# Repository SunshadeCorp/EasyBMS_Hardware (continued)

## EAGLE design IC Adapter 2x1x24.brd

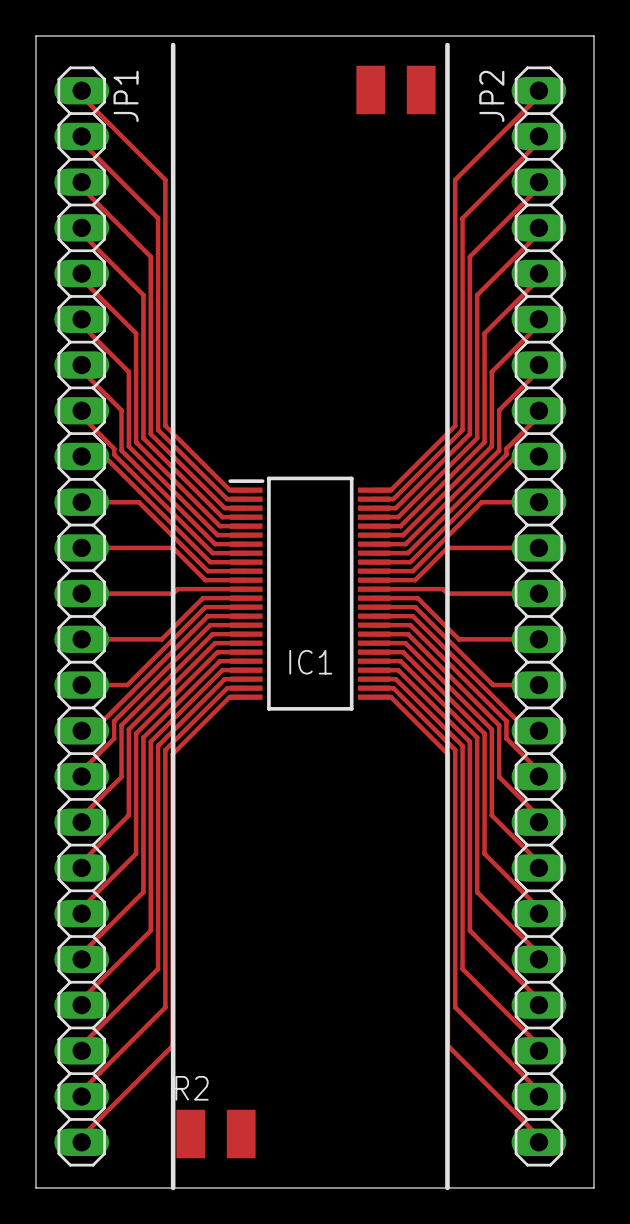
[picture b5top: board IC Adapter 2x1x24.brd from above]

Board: 2 copper layers, 31.0 x 64.0 mm, 5 parts (0 on the bottom side), 48 nets.

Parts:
IC1: LTC6804IG-1#PBF; SOP50P780X200-48N
JP1, JP2: 1X24
R1, R2: R1210

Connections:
C0: IC1.26, JP2.23
C1: IC1.24, JP1.24
C2: IC1.22, JP1.22
C3: IC1.20, JP1.20
C4: IC1.18, JP1.18
C5: IC1.16, JP1.16
C6: IC1.14, JP1.14
C7: IC1.12, JP1.12
C8: IC1.10, JP1.10
C9: IC1.8, JP1.8
C10: IC1.6, JP1.6
C11: IC1.4, JP1.4
C12: IC1.2, JP1.2
CPIO3: IC1.29, JP2.20
CSB: IC1.41, JP2.8
DRIVE: IC1.38, JP2.11
GPIO1: IC1.27, JP2.22
GPIO2: IC1.28, JP2.21
GPIO4: IC1.32, JP2.17
GPIO5: IC1.33, JP2.16
IBIAS: IC1.45, JP2.4
ICMP: IC1.46, JP2.3
IMB: IC1.47, JP2.2
IPB: IC1.48, JP2.1
ISOMD: IC1.40, JP2.9
S1: IC1.25, JP2.24
S2: IC1.23, JP1.23
S3: IC1.21, JP1.21
S4: IC1.19, JP1.19
S5: IC1.17, JP1.17
S6: IC1.15, JP1.15
S7: IC1.13, JP1.13
S8: IC1.11, JP1.11
S9: IC1.9, JP1.9
S10: IC1.7, JP1.7
S11: IC1.5, JP1.5
S12: IC1.3, JP1.3
SCK: IC1.42, JP2.7
SDI: IC1.43, JP2.6
SDO: IC1.44, JP2.5
SWTEN: IC1.36, JP2.13
V+: IC1.1, JP1.1
V-1: IC1.30, JP2.19
V-2: IC1.31, JP2.18
VREF1: IC1.35, JP2.14
VREF2: IC1.34, JP2.15
VREG: IC1.37, JP2.12
WDT: IC1.39, JP2.10

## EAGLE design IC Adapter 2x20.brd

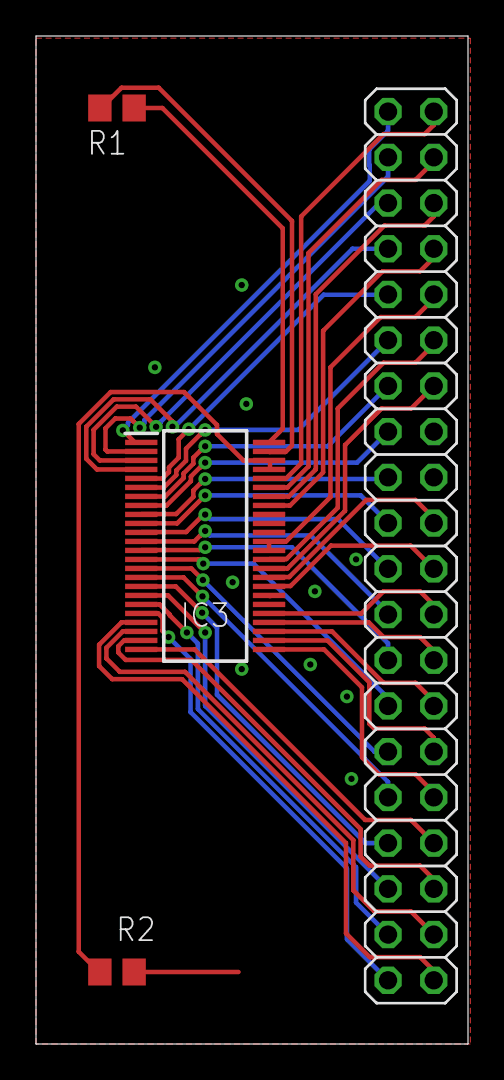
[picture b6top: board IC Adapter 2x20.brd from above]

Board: 2 copper layers, 24.0 x 56.0 mm, 4 parts (0 on the bottom side), 42 nets.

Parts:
IC3: LTC6804IG-1#PBF; SOP50P780X200-48N
JP1: 2X20
R1: 100R; R0805
R2: 20k; R0805

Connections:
C0: IC3.26, JP1.30
C1: IC3.24, JP1.34
C2: IC3.22, JP1.38
C3: IC3.20, JP1.39
C4: IC3.18, JP1.35
C5: IC3.16, JP1.31
C6: IC3.14, JP1.27
C7: IC3.12, JP1.23
C8: IC3.10, JP1.19
C9: IC3.8, JP1.15
C10: IC3.6, JP1.11
C11: IC3.4, JP1.7
C12: IC3.2, JP1.3
CSB: IC3.41, JP1.8
GND: IC3.30, IC3.31, IC3.40, JP1.16, JP1.18, R2.2
GPIO1: IC3.27, JP1.28
GPIO2: IC3.28, JP1.26
GPIO3: IC3.29, JP1.24
GPIO4: IC3.32, JP1.22
GPIO5: IC3.33, JP1.20
ICMP: IC3.45, IC3.46, R2.1
unnamed: IC3.48, R1.1
unnamed: IC3.47, R1.2
S1: IC3.25, JP1.32
S2: IC3.23, JP1.36
S3: IC3.21, JP1.40
S4: IC3.19, JP1.37
S5: IC3.17, JP1.33
S6: IC3.15, JP1.29
S7: IC3.13, JP1.25
S8: IC3.11, JP1.21
S9: IC3.9, JP1.17
S10: IC3.7, JP1.13
S11: IC3.5, JP1.9
S12: IC3.3, JP1.5
SCK: IC3.42, JP1.6
SDI: IC3.43, JP1.4
SDO: IC3.44, JP1.2
V+: IC3.1, JP1.1
VREF1: IC3.35, JP1.12
VREF2: IC3.34, JP1.14
VREG: IC3.36, IC3.37, JP1.10
